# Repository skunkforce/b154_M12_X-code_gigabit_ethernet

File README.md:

# edgy_board number b154
This design is part of the [edgy board project](https://github.com/skunkforce/edgy_boards). It provides a breakout of a M12 X-Coded connector.

# getting started
This repository uses submodules. After cloning use the command 

```$ git submodule update --init --recursive```

to pull the submodules before opening the project with kicad. 

# Tests
Tests can be found in [TESTS.md](TESTS.md)

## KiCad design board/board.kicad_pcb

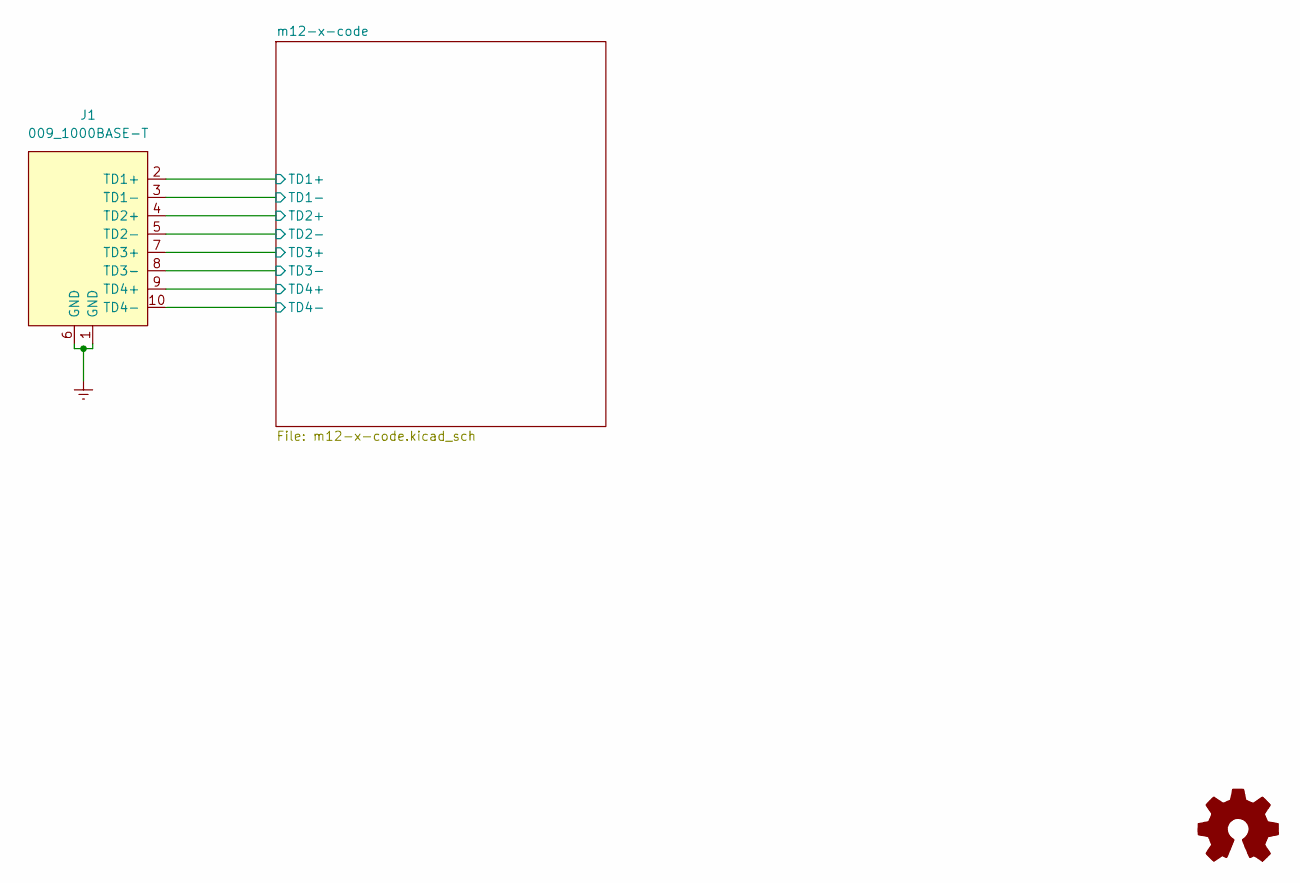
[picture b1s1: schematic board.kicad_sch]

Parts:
J1: 009_1000BASE-T; on_edge_2x05_device
LOGO1: Logo_Open_Hardware_Small; OSHW-Symbol_6.7x6mm_SilkScreen

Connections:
/m12-x-code/TD1+: J1.2 (TD1+); also elsewhere on the board
/m12-x-code/TD1-: J1.3 (TD1-); also elsewhere on the board
/m12-x-code/TD2+: J1.4 (TD2+); also elsewhere on the board
/m12-x-code/TD2-: J1.5 (TD2-); also elsewhere on the board
/m12-x-code/TD3+: J1.7 (TD3+); also elsewhere on the board
/m12-x-code/TD3-: J1.8 (TD3-); also elsewhere on the board
/m12-x-code/TD4+: J1.9 (TD4+); also elsewhere on the board
/m12-x-code/TD4-: J1.10 (TD4-); also elsewhere on the board
Earth: J1.1 (GND), J1.6 (GND)

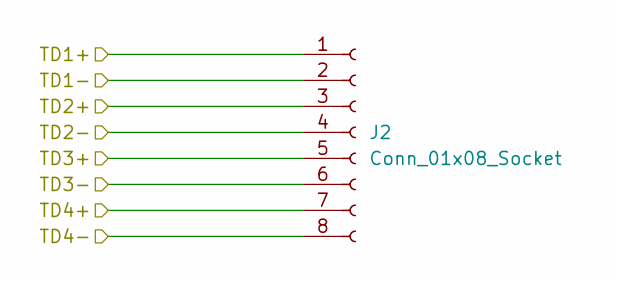
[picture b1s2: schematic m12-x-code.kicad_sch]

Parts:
J2: Conn_01x08_Socket; m12_x-code

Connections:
/m12-x-code/TD1+: J2.1; also elsewhere on the board
/m12-x-code/TD1-: J2.2; also elsewhere on the board
/m12-x-code/TD2+: J2.3; also elsewhere on the board
/m12-x-code/TD2-: J2.4; also elsewhere on the board
/m12-x-code/TD3+: J2.5; also elsewhere on the board
/m12-x-code/TD3-: J2.6; also elsewhere on the board
/m12-x-code/TD4+: J2.7; also elsewhere on the board
/m12-x-code/TD4-: J2.8; also elsewhere on the board

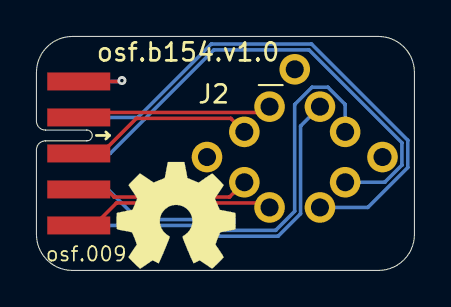
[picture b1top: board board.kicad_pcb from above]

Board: 2 copper layers, 21.0 x 13.0 mm, 3 parts (0 on the bottom side), 9 nets.

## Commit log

2024-02-03 initial
